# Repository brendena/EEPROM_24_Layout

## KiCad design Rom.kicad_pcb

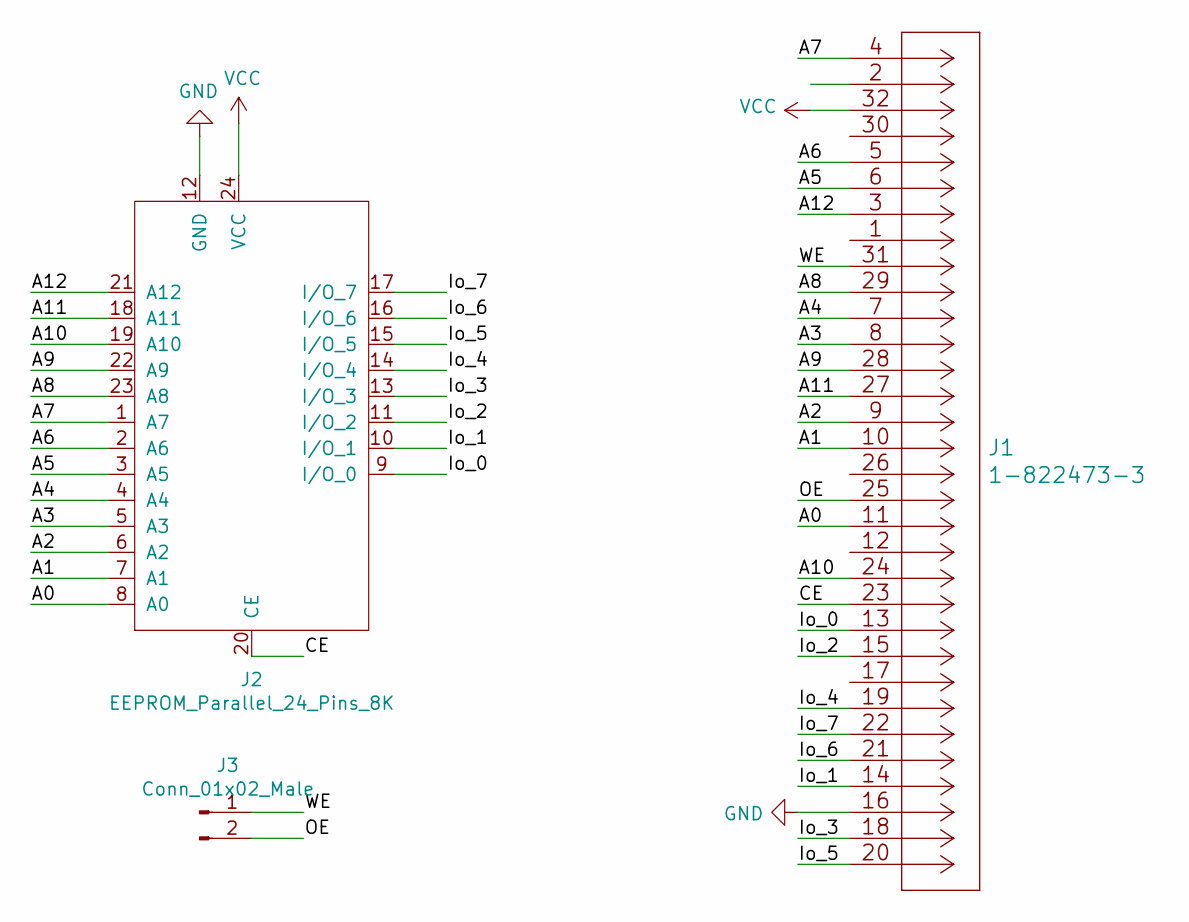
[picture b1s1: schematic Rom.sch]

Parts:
J1: 1-822473-3; PLCC_32_32_Small
J2: EEPROM_Parallel_24_Pins_8K; DIP-24_W15.24mm
J3: Conn_01x02_Male; PinHeader_1x02_P2.54mm_Vertical

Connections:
/A0: J1.11, J2.8 (A0)
/A1: J1.10, J2.7 (A1)
/A2: J1.9, J2.6 (A2)
/A3: J1.8, J2.5 (A3)
/A4: J1.7, J2.4 (A4)
/A5: J1.6, J2.3 (A5)
/A6: J1.5, J2.2 (A6)
/A7: J1.4, J2.1 (A7)
/A8: J1.29, J2.23 (A8)
/A9: J1.28, J2.22 (A9)
/A10: J1.24, J2.19 (A10)
/A11: J1.27, J2.18 (A11)
/A12: J1.3, J2.21 (A12)
/CE: J1.23, J2.20 (CE)
/Io_0: J1.13, J2.9 (I/O_0)
/Io_1: J1.14, J2.10 (I/O_1)
/Io_2: J1.15, J2.11 (I/O_2)
/Io_3: J1.18, J2.13 (I/O_3)
/Io_4: J1.19, J2.14 (I/O_4)
/Io_5: J1.20, J2.15 (I/O_5)
/Io_6: J1.21, J2.16 (I/O_6)
/Io_7: J1.22, J2.17 (I/O_7)
/OE: J1.25, J3.2
/WE: J1.31, J3.1
GND: J1.16, J2.12 (GND)
VCC: J1.32, J2.24 (VCC)

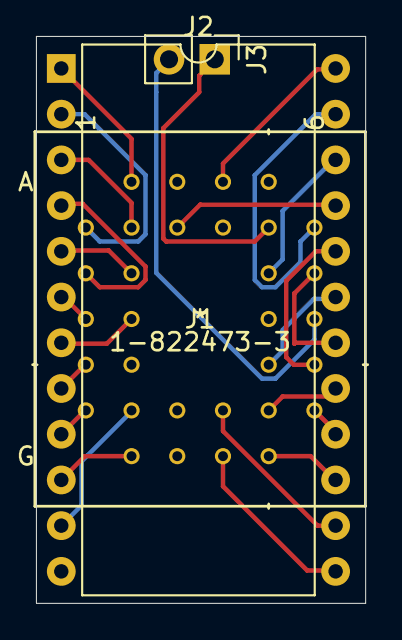
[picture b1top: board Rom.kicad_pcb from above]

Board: 2 copper layers, 18.3 x 31.5 mm, 3 parts (0 on the bottom side), 26 nets.

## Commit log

2020-12-13 added the first attempt

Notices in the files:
parts and their libraries:
Copyright 2016 Accelerated Designs. All rights reserved.
